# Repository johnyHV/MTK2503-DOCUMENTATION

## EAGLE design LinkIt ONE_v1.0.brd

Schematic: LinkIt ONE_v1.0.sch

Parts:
C1, C2, C11, C12, C34, C35, C45, C46, C60, C151, C152: 4.7uF; C0805
C3, C4, C5, C7, C14, C18, C19, C21, C28, C40, C44, C55, C58, C66, C77, C87, C90, C97, C101, C105, C106, C108, C127: 100nF; C0402
C6, C8, C9, C10, C13, C15, C16, C22, C23, C26, C29, C36, C37, C38, C39, C47, C48, C63, C65, C69, C70, C71, C72, C91, C92, C93, C94, C95, C96, C98, C104, C109, C116, C120, C139: 1uF; C0402
C17, C24, C25, C80, C85, C118, C137, C138, C143, C144, C145: 18pF; C0402
C20, C43: 1nF; C0402
C27, C68, C82, C83, C124, C125, C141: DNP/18pF; C0402
C30, C33: SMD CAP Tantalum 470uF-6.3V;D; AVX-D
C31: 220nF; C0402
C32, C51, C52, C74, C79, C128, C153, C154, C155: 22uF; C0805
C41, C73, C99: 2.2uF; C0603
C42: DNP/100nF; C0402
C49, C50, C88, C156: SMD CAP Tantalum 47uF-10V;B; AVX-B
C53, C54: 390pF; C0402
C56, C57: 33pF; C0402
C59: 100pF; C0402
C61, C62, C64: 27pF; C0402
C67, C84, C110, C115, C142: 1.2pF; C0402
C75, C76: 22pF; C0402
C78: 15pF; C0402
C81: 330pF; C0402
C89, C102, C103: DNP/22pF; C0402
C100: 22nF; C0402
C107, C148: DNP/EECENOF204Rk; 2P-D6.8MMX1.8MMH
C111, C113: 1.5pF; C0402
C112: 1.8pF; C0402
C114: 0.5pF; C0402
C117: DNP/0.5pF; C0402
C119, C158: 33nF; C0402
C122: DNP/4.7uF; C0805
C126, C129, C130: 39pF; C0402
C131: 220pF; C0402
C132: 1pF; C0402
C133: DNP/2.7pF; C0402
C134, C135: 2.2pF; C0402
C136: 1.5nF; C0402
C140: 10pF; C0402
C157: 4.7nF; C0402
D1, D15: SS0520-7-F; SOD123
D2: MMSZ4689-V; SOD123-2.7X1.6
D3, D4, D6: CESD5V0AP; SOT23
D7: SS14; D2010
DN: USB_DP; TP_4545
DP: USB_DN; TP_4545
GPS: U-FL Connector; 4P-U-FL
GSM: U-FL Connector; 4P-U-FL
J1, J11: SMD Grove;4P-2.0; 4P-SMD-2.0
J2: JST; JST-SMD-2.0-90D
J4: TF+SIM-VSHO-21-3301; 16P-L17.4MM*W16.5MM*H2.7MM
J7: Micro USB 5P without POST;ST-USB-001G; MICRO-USB
J16: 344017001; 8P-3.5-SMD
JTAG: DNP; 2*5P-2.0-TESTPOINT
L: GREEN; LED-0603
L1, L4, L16, L17, L19: 4.3nH; L0402
L2: Bead 120R-2A; L0603
L3, L6: LQM2MPN2R2MG0; 0806
L5: 6.8nH; L0402
L7: 1.5nH; L0402
L8, L13: SMD Power Inductor 10uH-20%;021042001; L0630
L9, L10: BLM15BD182SN1; L0402
L11: 100nH; L0603
L12: 1nH; L0402
L14: 1.8nH; L0402
L15: 4.7nH; L0402
L18: 3.3nH; L0402
L20: 22nH; L0603
L21, L22, L23: BLM18BD252SN1; L0603
L24: 470R-1000mA; L0805
P1, P2, P3, P4, P5, P6, P7, P8, P9, P10, P11, P12: PAD-MARK'ANNULAR'; ROUND-MARK-1.0
PWR: GREEN; LED-0603
Q1, Q2, Q3, Q4, Q8, Q9, Q10, Q11, Q12, Q13: CJ2302; SOT23
Q6, Q7: CJ2305; SOT23
Q14: S8550; SOT23
R1, R17, R18, R21, R22, R23, R25, R27, R28, R32, R38, R41, R51, R52, R54, R55, R60, R61, R79: 0R; R0402
R2, R6, R19, R20, R24, R33, R57, R69, R72, R74, R75, R84, R85, R87, R92, R96, R97, R108, R109: 10K; R0402
R3, R29, R53: 100K; R0402
R4: 49.9R-1%; R0402
R5: 910K; R0402
R7, R12, R36, R40, R49, R76, R77, R78, R81, R106, R107: 1K; R0402
R8, R13, R14: 1.5K; R0402
R10, R11, R39, R47, R63, R64, R65, R66, R68, R105: 100R; R0402
R15, R16: 470R; R0402
R26, R31, R80, R104: DNP/0R; R0402
R30: 3.9k; R0402
R34, R45, R50, R58, R59, R88, R89, R90: 33K-1%; R0402
R35: 8.2K-1%; R0402
R37, R110: DNP/10K; R0402
R46, R71, R73, R82, R83, R98, R99, R111, R112, R113, R114, R115, R116, R117, R118, R119: 4.7K; R0402
R48: 10R; R0402
R56, R91: 24K; R0402
R62: 68k; R0402
R67: DNP/1K; R0402
R70: 330K; R0402
R86: 39K; R0402
R93: 3.3K; R0402
R94: 0.2R-0805-1%; R0805
RESET: SMD Button;TS-1188E 6C81; 4P-SMD-7X3.5X3.5H
RST: RED; LED-0603
RX: RED; LED-0603
SW1, SW2: SWITCH-3P-SMD-6.6X2.8; 3P-SMD-2CH-6.6X2.8-REINFORCE
SW3: SWITCH-2CH-6P-2.54; 6P-2CH-2.54-7.6X3.0
TX: RED; LED-0603
U1: MT5931; TFBGA84
U2: MT3332; QFN48-6X6MM
U3: MX25U12835FZNI10G; WSON8-6X5X0.8H-W/HEAT
U4: XC6221B332MR-G; SOT-25J
U6: BCT4699; TQFN16
U7: MT2502A; VFBGA143
U8: NC/STT818B; SOT23-6L
U9: B8313; 5P-SMD-1.4X1.1MM
U10: SHIELDING-COVER; SHIELD-SMD-44.5X53.5
U11: PCB; ARDUINO-38P
U12: MP1496; TSOT23-8
U13: MAX2659; 6P-SMD-1.5X1.0X0.72H
U14: RF7198; 32P-SMD-RF1798-5.3MMX5.25MMX0.73H
U15: FB2012-05N2R4GT; 8P-SMD-2X1.25X0.7H
U16: uPG2176T5N; TSON6
U17: DNP/BAV70S; SOT363
U18: TXS0108PW; TSSOP20
U19: CJA1117B-3.3; SOT89
U20: ISL97516; MSOP8
VBAT_TP: VBAT; TP_4545
VCHG_5V1: PAD-TEST-POINT'4545'; TP_4545
VIO_28: PAD-TEST-POINT'4545'; TP_4545
WI-FI/BT: U-FL Connector; 4P-U-FL
X1: SMD Crystal 32.768KHZ-12.5pF-20ppm-80K; 2P-SMD-2.05X1.2
X2: 7L26002009; 2520
X3: 7M26000028/TXC; 4P-SMD-3.2X2.5

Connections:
2G_ANT: C82.1, R1.1, U14.19 (ANT)
2G_XTAL1: U7.B4 (XTAL1), X3.1
2G_XTAL2: U7.B5 (XTAL2), X3.3
5V_OUT: C1.1, C28.1, C90.1, C108.1, C154.1, C155.1, C156.+, J1.3, J11.3, L24.2, U11.28 (5V), U19.3 (IN)
/M_SCL: Q4.2 (S), R99.2, U7.B11 (SCL28)
/M_SDA: Q3.2 (S), R98.2, U7.C7 (SDA28)
/SPI_MISO: U6.7 (NO3), U18.8 (A7)
/SPI_MOSI: U6.15 (NO1), U18.7 (A6)
/SPI_SCL: R108.1, U6.3 (NO2), U18.9 (A8)
/SPI_SS: U7.B13 (CMPDN), U18.6 (A5)
ACCDET: R14.2, U7.K5 (ACCDET)
AD0/D14: R88.2, U11.19 (PC0/AD0/D14)
AD1/D15: R89.2, U11.20 (PC1/AD1/D15)
AD2/D16: R90.2, U11.21 (PC2/AD2/D16)
ADC3: U11.22 (PC3/AD3/D17)
ANTSEL_0: C143.1, U1.K8 (ANTSEL_0), U16.1 (VCONT1)
ANTSEL_1: C144.1, U1.J8 (ANTSEL_1), U16.3 (VCONT2)
APC_VBAIS: R57.2, U7.N7 (APC)
AUDIO_GND: D4.2, J16.2, R25.2
AVDD_SMPS: C12.1, C151.1, L2.2, U1.A2 (AVDD43_REF), U1.A4 (AVDD43_SMPS)
BANDSW: R60.2, U7.D5 (BPI_BUS0)
BATON: R84.1, U7.H5 (BATON)
BATTERY: C109.1, J2.+ (1), SW3.CH1A
BAT_CHARGE: R94.1, SW3.CH2A
BPI_BUS2: R67.2, R85.2, U7.A12 (BPI_BUS2)
BT_ANT: C110.1, C111.1, C145.2, L14.2
BT_LNA: C114.1, L12.1, U7.A6 (BT_LNA)
BUCK_VBAT: C78.2, C79.1, L13.1, R34.2, SW3.CH1B, SW3.CH2B
CHR_LDO: C48.1, Q1.1 (G), R93.2, U7.G5 (CHRLDO)
CLDO: C21.1, C22.1, U1.C1 (CLDO), U1.G4 (PAD_VDDK), U1.G6 (PAD_VDDK), U1.G7 (PAD_VDDK)
CMCSD0: U6.4 (COM2), U7.A13 (CMCSD0)
CMCSD1: U6.16 (COM1), U7.E5 (CMCSD1)
CMMCLK: U6.8 (COM3), U7.B9 (CMMCLK)
CMRST/EINT15: U7.B10 (CMRST), U18.3 (A2)
D8/GPIO48/EINT21: Q12.3 (D), R117.1, U11.9 (PB0/D8)
DRV: Q1.2 (S), U7.J2 (DRV)
EAR_EINT: R40.1, U7.A3 (EINT)
EINT_WIFI: R6.1, U1.E2 (WI-FI_INT_B), U7.C8 (CMCSK)
FB_OUT: C4.1, C88.+, C153.1, D7.-, L24.1, R62.1
FM_ANT_P-1: L11.1, R25.1, R104.1, U7.F2 (FM_ANT_P)
FREF_26M_WIFI: C20.1, U7.A5 (FREF)
GND: C1.2, C2.2, C3.2, C4.2, C5.2, C6.2, C7.2, C8.2, C9.2, C10.2, C11.2, C12.2, C13.1, C14.1, C15.2, C16.1, C17.1, C18.1, C19.1, C21.2, C22.2, C23.2, C26.2, C27.2, C28.2, C29.2, C30.-, C32.2, C33.-, C34.2, C35.2, C36.2, C37.2, C38.2, C39.2, C40.2, C41.2, C42.2, C44.2, C45.2, C46.2, C47.2, C48.2, C49.-, C50.-, C53.2, C54.2, C56.2, C57.2, C60.2, C61.2, C62.2, C63.2, C64.2, C65.2, C66.2, C68.2, C69.2, C70.2, C71.2, C72.2, C73.2, C74.2, C75.2, C76.2, C77.2, C79.2, C80.2, C81.2, C82.2, C83.2, C84.2, C87.2, C88.-, C89.2, C90.2, C91.2, C92.2, C93.2, C94.2, C95.2, C96.2, C97.2, C98.2, C99.2, C100.2, C101.2, C102.2, C103.2, C104.2, C106.2, C107.-, C108.2, C109.2, C110.2, C112.2, C113.2, C114.2, C115.2, C116.2, C117.2, C119.2, C120.2, C122.2, C124.2, C125.2, C126.1, C127.1, C128.1, C129.2, C130.2, C131.2, C132.2, C133.2, C134.2, C135.2, C136.2, C139.2, C140.2, C143.2, C144.2, C148.-, C151.2, C152.1, C153.2, C154.2, C155.2, C156.-, C157.1, C158.2, D2.1 (+), D3.3, D4.3, D6.3, GPS.GND1, GPS.GND2, GPS.GND3, GSM.GND1, GSM.GND2, GSM.GND3, J1.4, J1.SS1, J1.SS2, J2.3, J2.4, J2.- (2), J4.6 (VSS), J4.C5 (SIM_GND), J4.P1 (PAD1), J4.P2 (PAD2), J4.P3 (PAD3), J4.P4 (PAD4), J4.P5 (PAD5), J4.SB (SWITCH-B), J7.5 (GND), J7.S1 (GND), J7.S2 (GND), J7.S3 (GND), J7.S4 (GND), J7.S5 (GND), J7.S6 (GND), J11.4, J11.SS1, J11.SS2, JTAG.2, JTAG.3, L11.2, L15.1, L18.2, PWR.-, Q2.2 (S), R3.2, R5.2, R6.2, R15.2, R16.2, R19.1, R24.1, R29.1, R35.2, R45.2, R56.2, R58.2, R59.2, R75.1, R84.2, R85.1, R86.2, R91.1, R96.2, R97.2, R104.2, R109.1, R110.1, RESET.2, RESET.S1, RESET.S2, RX.-, SW1.SS1, SW1.SS2, SW1.SS3, SW1.SS4, SW2.B, SW2.SS1, SW2.SS2, SW2.SS3, SW2.SS4, TX.-, U1.A10 (AVSS33_PA), U1.B1 (GND_REF), U1.B3 (AGND43_SMPS), U1.B8 (AVSS16_VCO), U1.B9 (AVSS33_PA), U1.C5 (GND_PALDO), U1.C6 (AVSS16_WF), U1.C9 (AVSS33_PA), U1.D4 (AVSSRTC), U1.D6 (AVSS16_WF), U1.D7 (AVSS16_WF), U1.D9 (AVSS16_WF), U1.E1 (FSOURCE), U1.F4 (CGND), U1.F6 (CGND), U1.F7 (CGND), U1.J9 (XTEST), U1.K1 (CGND), U2.8 (AVSS43_MISC), U2.14 (AVSS43_DCV), U2.29 (GND), U2.46 (XTEST), U2.PAD (HEAT), U3.4 (GND), U3.PAD, U4.2 (VSS), U6.6 (GND), U6.PAD, U7.A2 (AVSS_2GHF), U7.A8 (AVSS_2GHF), U7.B6 (AVSS_2GHF), U7.C5 (AVSS_2GHF), U7.D2 (AVSS_2GHF), U7.D3 (AVSS_2GHF), U7.D4 (EXT_CLK_SEL), U7.E2 (AVSS44_ALDO), U7.F4 (TESTMODE), U7.F5 (GND), U7.F6 (GND), U7.F7 (GND), U7.G2 (AVSS_FM), U7.G6 (GND), U7.G7 (GND), U7.H6 (GND), U7.H7 (GND), U7.H8 (GND), U7.J5 (AVSS44_PMU), U7.J6 (AVSS28_ABB), U7.J7 (GND), U7.J8 (GND), U7.K1 (AVSS44_PMU), U7.K6 (GND), U7.L1 (AVSS44_BOOST), U7.L2 (AVSS44_BOOST), U7.M3 (AVSS_SPK), U7.M11 (GND), U7.N8 (RTC_XOSC32_ENB), U7.N9 (AVSS44_DLDO), U7.P2 (AVSS_SPK), U9.2 (GND), U9.3 (GND), U9.5 (GND), U10.1, U10.2, U10.3, U10.4, U10.5, U10.6, U10.7, U10.8, U10.9, U10.10, U11.15 (GND), U11.26 (GND), U11.27 (GND), U11.35 (GND), U12.4 (GND), U13.1 (GND), U13.2 (GND), U14.1 (GND), U14.2 (GND), U14.5 (GND), U14.6 (GND), U14.8 (GND), U14.9 (GND), U14.10 (GND), U14.11 (GND), U14.12 (GND), U14.13 (GND), U14.18 (GND), U14.20 (GND), U14.21 (GND), U14.22 (GND), U14.23 (GND), U14.24 (GND), U14.25 (GND), U14.28 (GND), U14.32 (GND), U14.33 (GND), U14.34 (GND), U14.35 (GND), U14.36 (GND), U15.4 (GND), U15.6 (GND), U15.8 (GND), U16.5 (GND), U16.PAD (GND), U18.11 (GND), U19.1 (GND), U20.4 (GND), U20.7 (FSEL), WI-FI/BT.GND1, WI-FI/BT.GND2, WI-FI/BT.GND3, X2.1, X2.2, X3.2, X3.4
GNSS_CORE_1V1: C37.1, C41.1, C42.1, U2.6 (DVDD11_CORE1), U2.13 (AVDD11_CLDO), U2.24 (DVDD11_CORE2), U2.43 (DVDD11_CORE3)
GNSS_DCV: L3.1, U2.15 (DCV)
GNSS_DCV_1V8: C34.1, C44.1, L3.2, R80.1, U2.1 (AVDD18_RXFE), U2.4 (AVDD18_CM), U2.12 (AVDD28_CLDO), U2.17 (DCV_FB)
GNSS_EN: U4.3 (CE), U7.D8 (KCOL0)
GNSS_FRAME_SYNC: R26.1, R65.1, U7.B12 (KCOL1)
GNSS_HRST: R52.1, U7.H12 (SIM2_SCLK)
GNSS_REF: C38.1, U2.7 (VREF)
GNSS_TXIND: U2.25 (TX1/TXIND/RTS0/MM_I2CD/CXO_CS/GIO1), U7.E6 (KCOL2)
GNSS_UART_RX: U2.35 (RX0/MM_I2CC/H_SPI_SI), U7.E13 (KROW4)
GNSS_UART_TX: R63.1, U2.37 (TX0/MM_I2CD/H_SPI_SO), U7.D10 (KCOL4)
GNSS_VGNSS_MAIN: C31.2, C35.1, C39.1, C46.1, U2.9 (AVDD43_VBAT), U2.16 (AVDD43_DCV), U4.5 (VOUT)
GNSS_VRTC_1V1: C31.1, C99.1, U2.18 (AVDD11_RTC)
GNSS_VRTC_4V3: C29.1, D1.-, R7.1, U2.19 (AVDD43_RTC)
GNSS_VTCXO_SW: C26.1, C80.1, C119.1, C120.1, L20.2, R41.2, U2.10 (AVDD_TCXO_SW), U13.4 (VCC), X2.4
GNSS_VTLDO: C36.1, C40.1, R31.1, U2.11 (AVDD28_TLDO), U2.30 (DVDD28_IO1), U2.42 (DVDD28_IO2)
GPIO0/ADC0/U3RX: C103.1, R59.1, R88.1, U7.F8 (GPIO_0), U17.4
GPIO1/ADC1/U3TX: C102.1, R58.1, R89.1, U7.E12 (GPIO_1), U17.5
GPIO2/ADC2/PWM0: C89.1, R45.1, R90.1, U7.D11 (GPIO_2), U17.2
GPIO13/EINT11/PWM0: R64.1, U7.D12 (KCOL3), U18.4 (A3)
GPIO19/PWM1: R66.1, U7.C11 (KROW2), U18.5 (A4)
GPIO40/SIM2_SIO: Q10.2 (S), R112.2, U7.J12 (SIM2_SIO)
GPIO_3/PWM1: U7.D13 (GPIO_3), U18.1 (A1)
GPS_RFIN: C67.2, L18.1, U2.48 (RF_IN)
GPS_RTC_32K: U2.21 (XIN), U7.J11 (SIM2_SRST)
ISENSE: Q14.3 (C), R94.2, U7.H2 (ISENSE), U8.1 (C), U8.2 (C), U8.5 (C), U8.6 (C)
JTAG_2V8: JTAG.1, R38.2
JTCK: JTAG.9, R65.2
JTDI: JTAG.7, R63.2
JTDO: JTAG.8, R66.2
JTMS: JTAG.10, R64.2
JTRST_B: JTAG.6, R39.2
JTRTCK: JTAG.4, R68.1
LPTE_MUX: Q13.2 (S), R118.2, U7.J10 (LPTE)
LSA0_LCM: R24.2, R37.2, U7.J9 (LSA0)
LSCE_B/EINT20: Q11.2 (S), R114.2, U7.G9 (LSCE_B)
LSCK_LCM: R97.1, U7.L10 (LSCK)
LSDA_LCM/EINT21: Q12.2 (S), R115.2, U7.L11 (LSDA)
LSRSTB: R96.1, U7.H9 (LSRSTB)
MC2_CLK: J4.5 (SD_CLK), U6.1 (NC1)
MC2_CMD: J4.3 (CMD), U6.5 (NC2)
MC2_DA0: J4.7 (DAT0), U6.9 (NC3)
MCINS: J4.SA (SWITCH-A), U7.D7 (KROW0)
MIC1_N: C55.1, U7.N5 (AU_VIN1_N)
MIC1_P: C58.1, U7.P5 (AU_VIN1_P)
MICBIAS0: R12.2, U7.L4 (AU_MICBIAS0)
MP3_OUTL: L9.1, U7.P1 (AU_HPL)
MP3_OUTR: L10.1, U7.N1 (AU_HPR)
M_SCL: Q4.3 (D), R23.2, R73.1, U11.18 (SCL), U11.24 (PC5/AD5/D19/SCL)
M_SDA: Q3.3 (D), R22.2, R71.1, U11.17 (SDA), U11.23 (PC4/AD4/D18/SDA)
unnamed: R87.1, U1.F8 (ANTSEL_3)
unnamed: C27.1, C85.1, R79.1
unnamed: R92.1, U1.G9 (ANTSEL_2)
unnamed: R69.2, U18.10 (OE)
unnamed: J4.1 (DAT2), R74.2
unnamed: C24.1, U9.1 (INPUT)
unnamed: C6.1, U1.A1 (REF)
unnamed: C20.2, U1.A7 (OSC_IN)
unnamed: C15.1, R4.2, U1.A6 (AVDD33_XO)
unnamed: C85.2, GPS.D, L20.1
unnamed: J1.1, R28.1
unnamed: L6.2, U1.A3 (LXBK)
unnamed: L5.2, U13.3 (RFIN)
unnamed: C25.1, U9.4 (OUTPUT)
unnamed: J11.1, R23.1
unnamed: C43.1, U2.5 (OSC)
unnamed: C148.+, R7.2
unnamed: R41.1, U13.5 (!SHDN)
unnamed: R19.2, SW1.B
unnamed: D7.+, L8.2, U20.5 (LX)
unnamed: J1.2, R27.1
unnamed: C51.1, L9.2
unnamed: C52.1, L10.2
unnamed: C51.2, R10.1
unnamed: C52.2, R11.1
unnamed: C55.2, C57.1, C59.2, C60.1, R12.1, R13.2
unnamed: C96.1, U7.N10 (VIBR)
unnamed: Q6.3 (D), RX.+
unnamed: R47.1, U7.H10 (RESETB)
unnamed: D15.-, U11.30 (RESET)
unnamed: C84.1, R21.1, WI-FI/BT.D
unnamed: R33.2, U12.6 (EN/SYNC)
unnamed: R30.2, U20.1 (COMP)
unnamed: C157.2, R30.1
unnamed: R62.2, R91.2, U20.2 (FB)
unnamed: Q6.2 (S), R76.1
unnamed: J11.2, R22.1
unnamed: J4.2 (CD/DAT3), R2.2
unnamed: C115.1, C137.1, R21.2
unnamed: Q7.2 (S), R77.1
unnamed: R48.1, U12.5 (BS)
unnamed: C105.2, R48.2
unnamed: R50.1, U12.8 (FB)
unnamed: C77.1, U12.7 (VCC)
unnamed: C78.1, R51.2
unnamed: C104.1, U7.D1 (VRF)
unnamed: C105.1, L13.2, U12.3 (SW)
unnamed: C100.1, U12.1 (SS)
unnamed: R34.1, R35.1, R50.2, R51.1
unnamed: J16.1, L21.2
unnamed: PWR.+, R78.1
unnamed: R36.1, RST.+
unnamed: R52.2, U2.47 (HRST_B)
unnamed: C158.1, U20.8 (SS)
unnamed: J4.8 (DAT1), R72.2
unnamed: R26.2, U2.33 (FRAME_SYNNC/DBG_RX/GIO8)
unnamed: C113.1, L4.1, L12.2, L14.1
unnamed: C112.1, L4.2
unnamed: C43.2, X2.3
unnamed: C25.2, L5.1
unnamed: C111.2, L15.2
unnamed: C118.1, U13.6 (RFOUT)
unnamed: C67.1, C68.1, C118.2
unnamed: R31.2, U2.32 (RX2/SPI_SI/JDI/DBG_RX/BSI_CK/GIO2)
unnamed: R80.2, U2.40 (BSI_CS/MM_I2CD/DUTY_CYCLE/PPS/GIO7)
unnamed: J16.6, R40.2, R53.1
unnamed: C124.1, GSM.D, R54.1
unnamed: C83.1, C125.1, R1.2, R54.2
unnamed: C130.1, R55.1, U14.31 (TX_EN)
unnamed: C131.1, R56.1, R57.1, U14.30 (VRAMP)
unnamed: C132.1, L17.1, U14.16 (RX_LB)
unnamed: C133.1, L19.1, U14.15 (RX_HB)
unnamed: Q1.3 (D), Q14.1 (B), U8.3 (B)
unnamed: L1.1, U14.4 (RFIN_LB)
unnamed: L16.1, U14.3 (RFIN_HB)
unnamed: C136.1, U14.7 (VBAT2)
unnamed: C129.1, R60.1, U14.29 (SW1)
unnamed: C93.1, C107.+, R8.2
unnamed: C138.2, U15.1 (UNBALANCED_PORT)
unnamed: Q7.3 (D), TX.+
unnamed: C138.1, U16.6 (OUTPUT1)
unnamed: C145.1, U16.4 (OUTPUT2)
unnamed: C137.2, U16.2 (INPUT)
unnamed: L.+, R49.1
unnamed: L.-, Q2.3 (D)
unnamed: R20.2, SW1.A
unnamed: R105.2, SW2.A, SW2.COM
unnamed: C24.2, C117.1, R79.2
unnamed: J16.4, L22.2
unnamed: J16.3, J16.7, L23.2
unnamed: Q6.1 (G), R106.1
unnamed: Q7.1 (G), R107.1
unnamed: Q2.1 (G), R29.2, R108.2
unnamed: R109.2, U2.31 (SCK1/SPI_SCK/GIO4)
unnamed: R110.2, U2.41 (SCS1#/SPI_SCS#/BSI_DATA/SYNC_PULSE/GIO5)
PALDO_3V3: C18.2, C139.1, C140.1, C152.2, R4.1, U1.A5 (PALDO), U1.A9 (AVDD33_TX), U1.E5 (PALDO_FB), U15.2 (NC/DC_FEED)
PB1/D9/PWM1: U11.10 (PB1/D9/PWM), U18.16 (B4)
PD0/RX: Q9.3 (D), R28.2, R111.1, U11.1 (PD0/D0/RX)
PD1/TX: Q8.3 (D), R27.2, R83.1, U11.2 (PD1/D1/TX)
PD2/INT0: Q11.3 (D), R116.1, U11.3 (PD2/D2/INT0)
PD3/INT1/PWM0: U11.4 (PD3/D3/INT1/PWM), U18.17 (B3)
PD4: Q10.3 (D), R113.1, U11.5 (PD4/D4)
PD5/PWM: U11.6 (PD5/D5/PWM), U18.20 (B1)
PD6/PWM: U11.7 (PD6/D6/PWM), U18.18 (B2)
PD7: Q13.3 (D), R119.1, U11.8 (PD7/D7)
PWRKEY: R105.1, U7.G4 (PWRKEY)
RESET: C81.1, D15.+, JTAG.5, R47.2, R81.1, RESET.1, RST.-
RXHB_P: L19.2, U7.B1 (RXHB)
RXLB_P: L17.2, U7.A1 (RXLB)
SIM1_SCLK: C62.1, J4.C3 (SIM_CLK), U7.K7 (SIM1_SCLK)
SIM1_SIO: C64.1, J4.C7 (I/O), U7.L9 (SIM1_SIO)
SIM1_SRST: C61.1, J4.C2 (RST), U7.K8 (SIM1_SRST)
SMPSLDO_1V6: C11.1, C13.2, C16.2, C17.2, C19.2, L6.1, U1.A8 (AVDD16_SX), U1.C2 (AVDD16_CLDO), U1.C3 (OUT_FB), U1.D10 (AVDD16_TRX), U1.E10 (AVDD16_LF)
SPI_MISO: U11.13 (PB4/D12/MISO), U11.38 (MISO), U18.13 (B7)
SPI_MOSI: U11.12 (PB3/D11/MOSI/PWM), U11.34 (MOSI), U18.14 (B6)
SPI_SCL: U11.14 (PB5/D13/SCK), U11.37 (SCK), U18.12 (B8)
SPI_SS: U11.11 (PB2/D10/SS/PWM), U18.15 (B5)
SQI_CE: U3.1 (CS#), U7.G13 (SFSCS0)
SQI_SCK: U3.6 (SCLK), U7.G8 (SFSCK)
SQI_SI: U3.5 (SI/SIO0), U7.F9 (SFSOUT)
SQI_SIO2: U3.3 (WP#/SIO2), U7.F12 (SFSWP)
SQI_SIO3: U3.7 (RESET#SIO3), U7.F10 (SFSHOLD)
SQI_SO: U3.2 (SO/SIO1), U7.G12 (SFSIN)
SW_SPI/SDIO: SW1.COM, U6.2 (INA), U6.10 (INB)
TRX_IO_N: C142.1, L7.2, U1.C10 (TRX_IO_N)
TRX_IO_P: C142.2, R61.2, U1.B10 (TRX_IO_P)
TR_N: C141.1, L7.1, U15.7 (BALANCED_PORT)
TR_P: C141.2, R61.1, U15.5 (BALANCED_PORT)
TXO_HB: C134.1, L16.2, U7.C2 (TX_HB)
TXO_LB: C135.1, L1.2, U7.B2 (TX_LB)
TX_EN: R55.2, R75.2, U7.A9 (BPI_BUS1)
UART1_RX: Q9.2 (S), R82.2, R106.2, U7.E9 (URXD1)
UART1_TX: Q8.2 (S), R46.2, R107.2, U7.E8 (UTXD1)
USBD_N: D6.1, R17.2, U7.N11 (USB11_DM)
USBD_P: D6.2, R18.2, U7.P11 (USB11_DP)
USB_5V: C49.+, C74.1, C98.1, C106.1, C116.1, J7.1 (VCC), Q14.2 (E), R33.1, R70.1, R93.1, U8.4 (E), U12.2 (IN), VCHG_5V1.T
USB_N: DP.T, J7.2 (DM), R17.1
USB_P: DN.T, J7.3 (DP), R18.1
VA: C94.1, U7.P3 (VA)
VBAT: C3.1, C8.1, C30.+, C33.+, C45.1, C50.+, C72.1, C73.1, C101.1, C126.2, C127.2, C128.2, D2.2 (-), L2.1, L8.1, R78.2, SW3.COM1, SW3.COM2, U4.1 (VIN), U7.E1 (VBAT_VA), U7.H1 (BATSNS), U7.L3 (AVDD_SPK), U7.M10 (VBAT_DIGITAL), U14.26 (VBAT1), U20.3 (EN), U20.6 (VDD), VBAT_TP.T
VCDT: R70.2, R86.1, U7.J4 (VCDT)
VCORE: C69.1, U7.A11 (VDDK), U7.P9 (VCORE)
VIO18_LDO: C70.1, Q11.1 (G), Q12.1 (G), Q13.1 (G), R37.1, R114.1, R115.1, R118.1, U7.N13 (VIO18), U7.P13 (VIO18)
VIO28_LDO: C5.1, C14.2, C23.1, C63.1, C71.1, C122.1, Q3.1 (G), Q4.1 (G), Q8.1 (G), Q9.1 (G), Q10.1 (G), R36.2, R38.1, R46.1, R49.2, R53.2, R67.1, R69.1, R76.2, R77.2, R81.2, R82.1, R87.2, R92.2, R98.1, R99.1, R112.1, U1.D3 (AVDDRTC), U1.H1 (DVDDIO3), U1.J7 (DVDDIO2), U1.K7 (DVDDIO1), U1.K10 (DVDDIO0), U7.B7 (AVDD15_BTRF), U7.B8 (VIO28), U17.3, U17.6, U18.2 (VCCA), VIO_28.T
VIO33_LDO: C2.1, C7.1, C32.1, C87.1, R20.1, R71.2, R73.2, R83.2, R111.2, R113.2, R116.2, R117.2, R119.2, U6.14 (VCC), U11.29 (3V3), U11.31 (ADC7), U18.19 (VCCB), U19.2 (OUT), U19.4 (OUT)
VMC: C66.1, C95.1, J4.4 (VDD), R2.1, R72.1, R74.1, U7.K9 (VMC)
VREF: C92.1, U7.G1 (VREF)
VRTC: D1.+, R8.1, U7.P8 (VRTC)
VSF: C47.1, C91.1, U3.8 (VCC), U7.F11 (VSF)
VSIM1: C65.1, C97.1, J4.C1 (VCC), J4.C6 (VPP), U7.L7 (VSIM1)
VSIM2: C9.1, U7.H13 (VSIM2)
VUSB: C10.1, U7.P12 (VUSB)
WIFI_BT_PRI: R5.1, R68.2, U1.H7 (BT_PRI), U7.C12 (KROW1)
WIFI_EN: R3.1, U1.B5 (PAD_EN), U7.C3 (GPIO_10)
WIFI_MC1CLK: U1.J2 (OE_N), U7.K12 (MCCK)
WIFI_MC1CMD: U1.J1 (A0), U7.L13 (MCCM0)
WIFI_MC1DA0: U1.H3 (D0), U7.K13 (MCDA0)
WIFI_MC1DA1: U1.J3 (D1), U7.M12 (MCDA1)
WIFI_MC1DA2: U1.H2 (D2), U7.L12 (MCDA2)
WIFI_MC1DA3: U1.K2 (D3), U7.N12 (MCDA3)
WIFI_OSC_EN: U1.F9 (OSC_EN), U7.B3 (SRCLKENAI)
WIFI_RST_N: U1.K9 (SYSRST_B), U7.C4 (GPIO_11)
WIFI_RTC: R32.2, R39.1, U7.E7 (KROW3)
WIFI_XIN: R32.1, U1.D1 (X32K_IN)
XIN: C75.1, U7.M7 (XIN), X1.1
XMIC: C56.1, C58.2, C59.1, D3.2, L21.1, R13.1, R14.1
XMP3_L: C54.1, D3.1, L22.1, R10.2, R16.1
XMP3_R: C53.1, D4.1, L23.1, R11.2, R15.1
XOUT: C76.1, U7.M6 (XOUT), X1.2

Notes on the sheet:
close to AVDD16_CLDO [C2]
close to AVDDRTC [D3]
close to AVDD16_LF [E10]
close to AVDD16_TRX [D10]
close to AVDD33_TX [A9]
close to AVDD16_SX [A8]
close to GPS AVDD43_DCV [PIN16]
close to GPS AVDD11_CLDO [PIN13]
SD Interface
Serial Flash
AUDIO
SIM
USB
GPIO Interface
UART Interface
SPI Interface
direct to GND plane of charge pump
SD Card/ SPI
IIC Interface
YiLong.Qin
Bruce Qin
v0.9
RESET KEY
WIFI
SYS CONFIG
IO INTERFACE CONFIG
POWER
EXTEND INTERFACE
GSM/GPRS
GPS
WIFI/BT
SERIAL FLASH & SD CARD
AUDIO INTERFACE
USB&SIM INTERFACE
C63 close to MT2502 B7
0:VSF 1V8
1:VSF 3V0
HW bootup
JTAG
KROW1

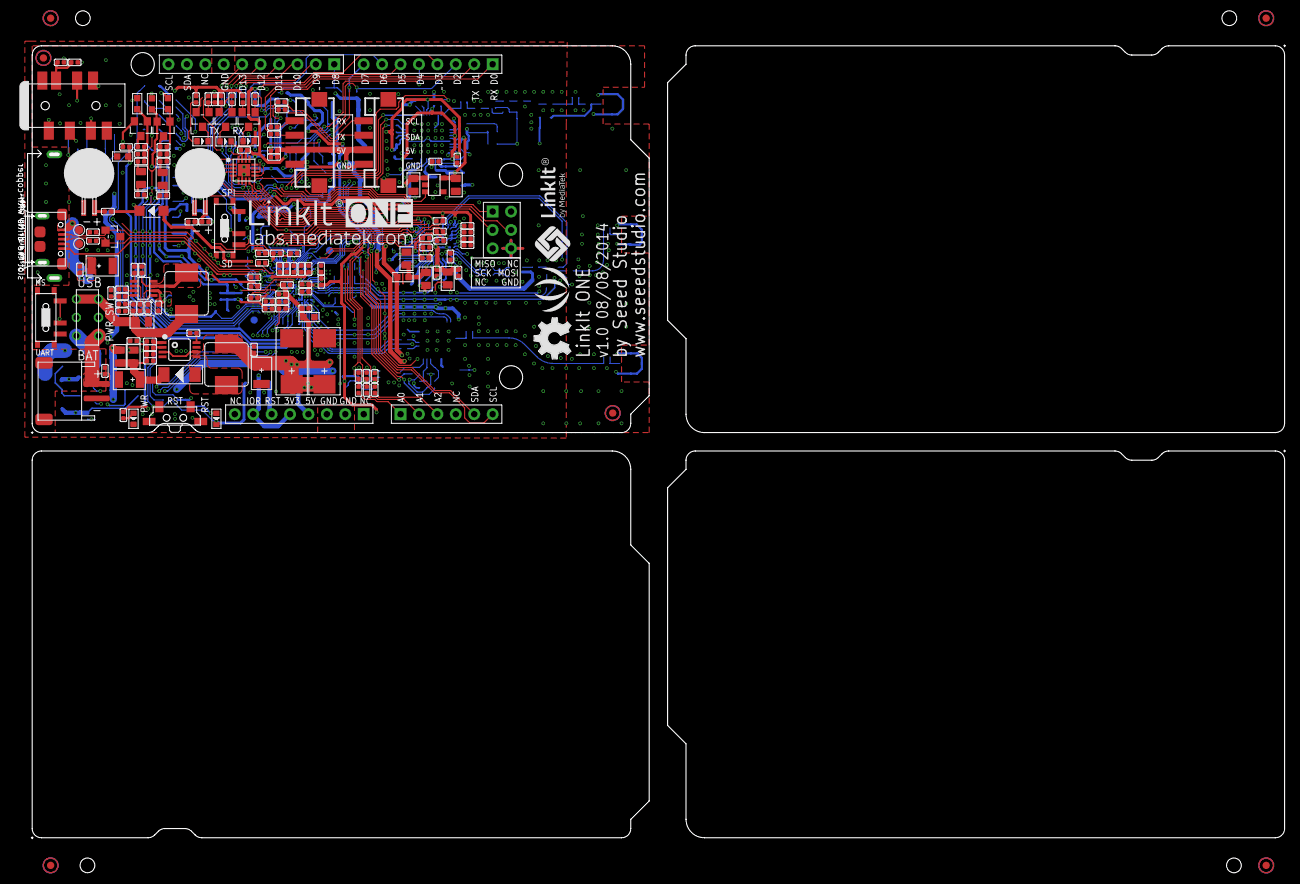
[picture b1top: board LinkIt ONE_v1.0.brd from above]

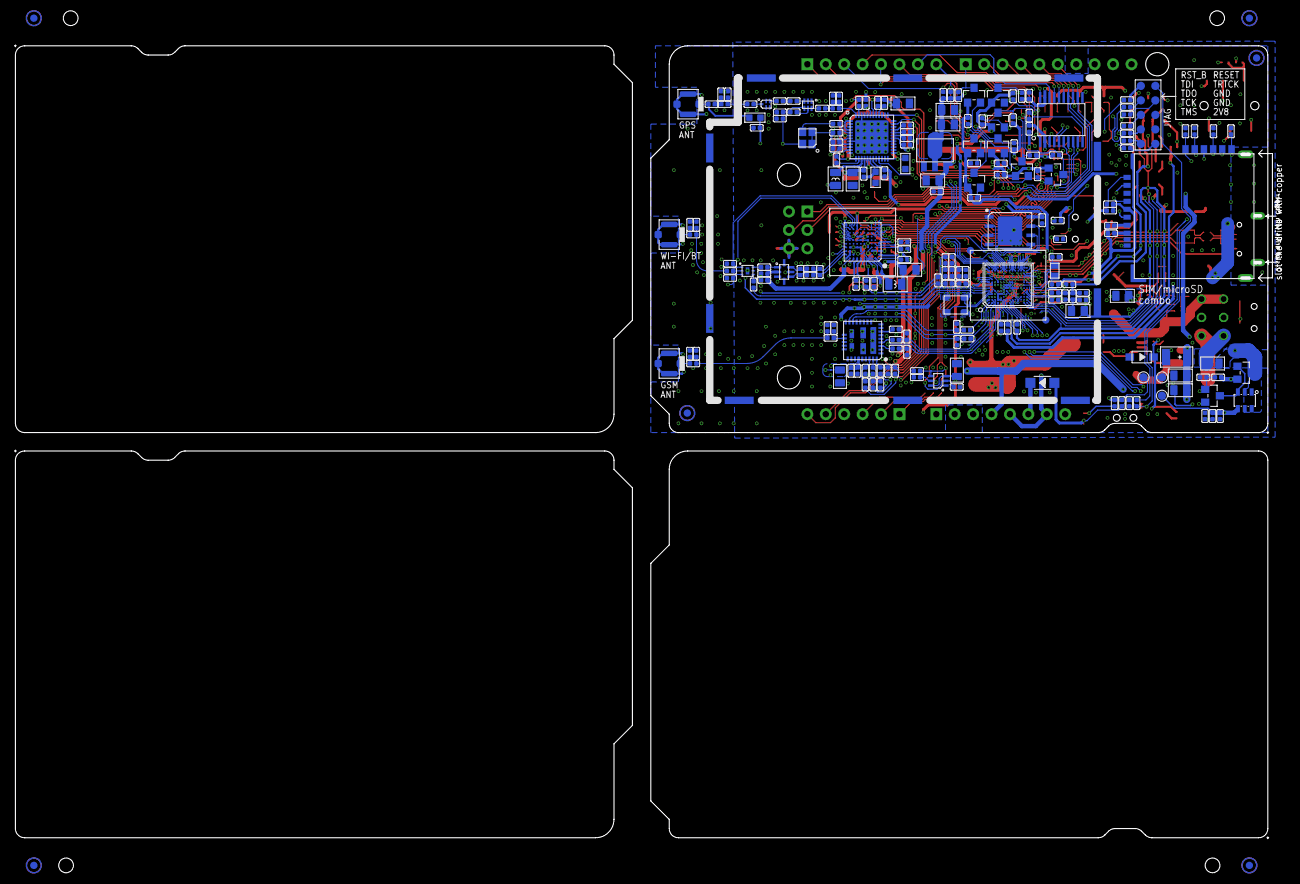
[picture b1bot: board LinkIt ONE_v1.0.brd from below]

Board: 4 copper layers, 174.0 x 109.5 mm, 367 parts (208 on the bottom side), 259 nets.

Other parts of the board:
U$13: OSHW_FILLX200_NOTEXT
U$14: MTK-LINKLTONE
U$15: BYMTK-200-1
U$18: LOGO_SILK

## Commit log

2019-01-23 add WZ=203CS
2019-01-24 add video tutorial
2020-03-20 - Ad video tutorial
2020-06-04 Add LinkIt One
